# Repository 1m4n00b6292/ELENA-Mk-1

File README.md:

# ELENA Mk.1

**ELENA Mk.1** is a Raspberry Pi HAT built around an **STM32H562RGT6** (Cortex-M33, LQFP64). It sits between a
Raspberry Pi (developed against a Pi 5) and the robot's low-level hardware:

- The **Pi talks to the MCU over SPI**: fixed 64-byte frames with CRC, the MCU as SPI slave, plus a data-ready line.
- A **UART link to the Pi (or a USB-UART adapter)** gives a text console for bring-up, quick debugging and manual control.
- The MCU drives **four UNIDRIVE wheel drivers over CAN** (250 kbit/s) and samples a **TDK ICM-42688-P IMU** at 1 kHz.
- The board takes a **24 V-class supply** and generates 5 V (also fed to the Pi) and 3.3 V on board.

The firmware runs on **FreeRTOS** and is built in layers (L1 BSP → L2 RTOS + bus drivers → L3 device drivers →
L4 Pi link + parameters → L5 control). The current version is **0.4.0 (L4)**: the Pi link, telemetry and the
parameter store work; motion commands over SPI are refused until the L5 control layer lands.

---

## Contents

- [Hardware](#hardware)
- [Firmware architecture](#firmware-architecture)
- [SPI link protocol (Pi ⇄ MCU)](#spi-link-protocol-pi--mcu)
- [UART console](#uart-console)
- [CAN: UNIDRIVE wheel drivers](#can-unidrive-wheel-drivers)
- [Parameters](#parameters)
- [Status LEDs and fault codes](#status-leds-and-fault-codes)
- [Build and flash](#build-and-flash)
- [Host unit tests](#host-unit-tests)
- [Pi-side tool: `elena_link.py`](#pi-side-tool-elena_linkpy)
- [Bench tests](#bench-tests)
- [Repository layout](#repository-layout)
- [Known issues and notes](#known-issues-and-notes)

---

## Hardware

Schematic: [`ELENA_Mk_1.pdf`](ELENA_Mk_1.pdf) (KiCad 10, five sheets: top level, Protection, DC_Power,
MCU_STM32H562RGT6, CAN_TRANSCEIVER).

### Block overview

```
 VIN (J1) ──► Protection ──► +24V ──► LMR51450 buck ──► +5V ──┬──► Pi 5V (J2 pin 2)
              LM74502 + 2x CSD18510Q5B                         ├──► TJA1051T CAN transceiver
              TVS3301, SMBJ5371B                               └──► AP2112K-3.3 ──► +3V3 (MCU)

 Raspberry Pi header (J2) ◄── SPI0 + DRDY ──► STM32H562RGT6 ◄── SPI3 + I2C1 ──► J4 sensor header (ICM-42688-P)
                          ◄── UART ───────►               ──── FDCAN1 ─────► TJA1051T ──► J5 CANH/CANL
                                                          ──── SWD ────────► J3
```

### Power

| Stage | Part | Notes |
| --- | --- | --- |
| Input | J1 (2-pin) | VIN with LED indicator |
| Reverse / over-voltage protection | LM74502H controller driving back-to-back CSD18510Q5B MOSFETs | OV threshold set by R3/R4 (100 k / 3.5 k); TVS3301 (37 V abs max) and SMBJ5371B on the input |
| 24 V → 5 V | LMR51450 synchronous buck, 4.7 µH | Output +5V, test point TP2 |
| 5 V → 3.3 V | AP2112K-3.3 LDO | Output +3V3, test point TP3 |

The +5V rail is connected to the Pi header's 5V pin, so the HAT can power the Pi.

### MCU and clocks

- STM32H562RGT6, 8 MHz crystal (Y1) on PH0/PH1, PLL to **168 MHz** SYSCLK.
- 1 MB flash, 640 KB RAM (per the linker script).
- BOOT0 strapped through R8 (10 k), 100 nF on NRST.

### Pinout highlights

| Function | MCU pin | Connects to | Firmware |
| --- | --- | --- | --- |
| SPI1 NSS | PA4 | Pi GPIO8 / CE0 (header pin 24) | SPI1 slave, hardware NSS input |
| SPI1 SCK | PA5 | Pi GPIO11 / SCLK (pin 23) | |
| SPI1 MISO | PA6 | Pi GPIO9 / MISO (pin 21) | |
| SPI1 MOSI | PA7 | Pi GPIO10 / MOSI (pin 19) | |
| SPI1 DRDY | PC4 | Pi GPIO7 (pin 26) | GPIO output, "response ready" |
| USART1 TX | PB14 | Pi GPIO15 / RXD (pin 10) | 115200 8N1 console |
| USART1 RX | PB15 | Pi GPIO14 / TXD (pin 8) | |
| FDCAN1 RX / TX | PA11 / PA12 | TJA1051T (U6) → J5 | Classic CAN, 250 kbit/s |
| SPI3 SCK / MISO / MOSI | PC10 / PC11 / PC12 | J4 | SPI master, 6 MHz, mode 0 |
| SPI3 CS1 / CS2 / CS3 | PD2 / PB3 / PB4 | J4 | GPIO chip selects (CS1 = IMU) |
| I2C1 SCL / SDA | PB6 / PB7 | J4 | Configured, not used yet |
| SWDIO / SWCLK | PA13 / PA14 | J3 | Debug |
| LED_1 … LED_4 | PC3, PC2, PC1, PC0 | D6, D5, D4, D3 (510 Ω to GND) | See [LEDs](#status-leds-and-fault-codes) |

### Connectors

| Ref | Type | Pins |
| --- | --- | --- |
| J1 | 1x2 | Power input |
| J2 | Raspberry Pi 40-pin | 5V, GND, SPI0 (GPIO8–11), GPIO7 (DRDY), UART (GPIO14/15) |
| J3 | 1x3 SWD | 1 SWDIO, 2 SWCLK, 3 GND |
| J4 | 2x5 sensor header | 1 SDA, 2 SCL, 3 SPI3_CS3, 4 SPI3_CS2, 5 GND, 6 +5V, 7 SPI3_CS1, 8 SPI3_MOSI, 9 SPI3_MISO, 10 SPI3_SCK |
| J5 | 1x2 CAN | CANH, CANL. 120 Ω termination (R13) selectable with jumper JP1 |

> **J4 supply:** J4 only carries +5V, but the ICM-42688-P is rated 3.6 V max. Power the IMU module from 3.3 V
> (see [Known issues](#known-issues-and-notes)).

### IMU

TDK ICM-42688-P on SPI3 / CS1 (datasheet: [`ds-000347-icm-42688-p-v1.6.pdf`](ds-000347-icm-42688-p-v1.6.pdf)).
Default setup: accel ±4 g, gyro ±500 dps, both at 1 kHz ODR, low-noise mode. J4 has no interrupt line, so the
firmware polls it every 1 ms with a 14-byte burst read (about 20 µs at 6 MHz).

---

## Firmware architecture

STM32CubeMX project (`ELENA_Mk1_FW_V1.ioc`) with CMake, HAL, and a vendored **FreeRTOS V11.1.0** kernel
(port `ARM_CM33_NTZ`, non-secure, no TrustZone, `heap_4`). Application code lives in `App/` and is layered:

| Layer | Folder | What it does |
| --- | --- | --- |
| L1 BSP | `App/bsp/` | Reset cause, CPU fault capture (register dump on UART, kept in backup SRAM across a reset), LEDs, µs time base (TIM2), polled debug UART, IWDG |
| L2 bus drivers | `App/drivers/bus/` | USART1 with DMA both ways, SPI3 master, FDCAN1 with RX filters and a TX ring, CRC-16 on the CRC peripheral plus software CRC-16/CRC-8 |
| L3 device drivers | `App/drivers/dev/` | ICM-42688-P, UNIDRIVE CAN protocol (pure packing/parsing) and node tracking |
| L4 comms | `App/comms/` | SPI frame format (pure code), SPI1 slave link with DRDY, parameter table and flash storage |
| App | `App/app/` | Tasks, self-test, bring-up shell and console commands, LED blink codes, link application glue |
| OS | `App/os/` | `FreeRTOSConfig.h`, RTOS hooks |

Pure code (`spi_proto.c`, `unidrive_proto.c`, `params.c`, `crc_sw.c`) has no HAL or RTOS dependency and is unit
tested on a PC.

### Tasks (firmware 0.4.0)

| Task | Priority | Job |
| --- | --- | --- |
| `link` | 6 | SPI1 slave link to the Pi: validate each frame, answer, re-arm DMA, raise DRDY |
| `imu` | 4 | Poll the ICM-42688-P at 1 kHz, publish the latest sample, re-check WHO_AM_I every 100 ms |
| `canrx` | 3 | Hand each received CAN frame to the UNIDRIVE driver |
| `boot` | 2 | Start bus drivers, load parameters, run the self-test, start the other tasks, then run the console shell |
| `hb` | 1 | Every 20 ms: kick the IWDG, update LED blink codes; toggle the heartbeat LED at 1 Hz |

L5 adds the control task (state machine, kinematics, fault manager).

### Boot self-test

At every boot the firmware checks: software and peripheral CRC-16 and CRC-8 against their check values, UART TX
through DMA, CAN internal loopback into both FIFOs, CAN hardware filter rejection, and the IMU WHO_AM_I (0x47).
The result prints on the console and a failed internal check shows as LED blink code 4-1. Run it again any time
with `selftest`.

### Build-time switches

`App/Inc/config.h`:

| Switch | Meaning |
| --- | --- |
| `CFG_IWDG_ENABLE`, `CFG_IWDG_TIMEOUT_MS` | Independent watchdog on/off, timeout (100 ms) |
| `CFG_IWDG_FREEZE_IN_DEBUG` | Freeze the IWDG while the debugger halts the core |
| `CFG_HOST_WDT_ENABLE`, `CFG_HOST_TIMEOUT_MS` | Raise HOST_TIMEOUT if no valid SPI frame for 500 ms (off for bench work without a Pi) |
| `CFG_CMD_STALE_MS` | Ramp to zero when the newest drive command is older than this |
| `CFG_FAULT_RESET` | After a CPU fault: 1 = reset, 0 = halt and blink LED_3 so a debugger can attach |
| `CFG_TRAP_DIV_BY_ZERO` | Trap integer divide by zero as a UsageFault |
| `CFG_DRV_EXPECTED_MASK` | Which wheel driver nodes must be present (0x0F = all four) |
| `CFG_LED_UART_RX` | LED_2 flashes on console RX (until L5 uses it for ARMED) |
| `CFG_TEST_FAULT`, `CFG_TEST_IWDG` | Bench-only: deliberate BusFault / hang 5 s after boot |

Enable both watchdogs before running on the robot.

---

## SPI link protocol (Pi ⇄ MCU)

The Pi is SPI master (SPI0, CE0, mode 0, 8-bit, MSB first; the Pi tool defaults to 4 MHz). The MCU is the slave on
SPI1 with hardware NSS.

### Transaction flow

1. The MCU has a 64-byte response loaded and both DMAs armed, then raises **DRDY** (PC4 → Pi GPIO7).
2. The Pi asserts CE0 and clocks exactly 64 bytes each way. NSS falling drops DRDY.
3. NSS rising wakes the `link` task: it checks that exactly 64 bytes arrived, validates and handles the command,
   builds the next response, re-arms DMA and raises DRDY again.

The response clocked out during a transfer was prepared after the **previous** transfer, so the answer to a command
arrives in the next transaction. A transfer of any other length is aborted, counted, and answered with ACK result 6
(`SHORT`).

### Frame format (64 bytes, all fields little-endian)

| Bytes | Field | Notes |
| --- | --- | --- |
| 0 | SOF | `0xA5` |
| 1 | VER | `0x01` |
| 2 | TYPE | See below |
| 3 | SEQ | Sequence number |
| 4 | LEN | Payload length, must match the TYPE exactly |
| 5 | FLAGS | Response: bit 0 another param reply waiting, bit 1 faults latched |
| 6..61 | Payload | 56 bytes, zero-padded |
| 62..63 | CRC | CRC-16/CCITT-FALSE (poly 0x1021, init 0xFFFF) over bytes 0..61 |

### Commands (Pi → MCU)

| TYPE | Name | LEN | Payload |
| --- | --- | --- | --- |
| `0x00` | POLL | 0 | |
| `0x01` | DRIVE_TWIST | 8 | `vx`, `vy`, `wz` (i16), `accel_max` (u16, 0 = use parameter) |
| `0x02` | WHEEL_SPEED | 8 | 4 × i16, 0.1 rpm |
| `0x03` | WHEEL_DUTY | 8 | 4 × i16, 0.01 % |
| `0x10` | ARM | 3 | key `0x4D52`, arm (u8) |
| `0x11` | ESTOP | 0 | |
| `0x12` | CLEAR_FAULTS | 4 | mask (u32) |
| `0x20` | SET_PARAM | 6 | id (u16), value (f32) |
| `0x21` | GET_PARAM | 2 | id (u16) |
| `0x22` | SAVE_PARAMS | 2 | key `0x5356` |
| `0x7F` | REBOOT | 3 | key `0x5242`, target (u8) |

SET_PARAM, SAVE_PARAMS and REBOOT are refused while armed. At L4 the robot cannot be armed: ARM, DRIVE_TWIST,
WHEEL_SPEED and WHEEL_DUTY are answered `REFUSED`; ESTOP and CLEAR_FAULTS go straight to the drivers.

### Responses (MCU → Pi)

**TELEMETRY (`0x80`)**, payload offsets:

| Offset | Field | Type / unit |
| --- | --- | --- |
| 0 | ack_seq | u8, SEQ of the command being acknowledged |
| 1 | ack_result | u8: 0 OK, 1 BAD_CRC (also bad SOF/VER), 2 UNKNOWN_TYPE, 3 BAD_LEN, 4 REFUSED, 5 BAD_KEY, 6 SHORT |
| 2 | state | u8: 0 BOOT, 1 DISARMED, 2 ARMED, 3 ESTOP, 4 FAULT |
| 3 | drv_online | u8 bit mask of wheel drivers |
| 4 | faults | u32 bit mask |
| 8 | time_us | u32 |
| 12 | acc[3] | i16 raw counts |
| 18 | gyr[3] | i16 raw counts |
| 24 | imu_temp | i16 raw (°C = raw / 132.48 + 25) |
| 26 | wheel_spd[4] | i16, 0.1 rpm |
| 34 | wheel_pos[4] | i32, unwrapped encoder counts |
| 50 | motor_i[4] | u8, 0.1 A magnitude |
| 54 | vbus | u16, 10 mV |

**PARAM_REPLY (`0x81`)**: id (u16), status (0 OK, 1 UNKNOWN, 2 RANGE, 3 READONLY, 4 ARMED), value (f32).

**Fault bits** set at L4: 3 IMU_FAIL, 4–7 DRV1–4_OFFLINE, 8–11 DRV1–4_FAULT, 12 CAN_BUS_OFF, 13 CAN_ERR_PASSIVE,
18 WDT_RESET, 19 PARAM_INVALID.

### Pi setup

```
# /boot/firmware/config.txt
dtparam=spi=on
dtoverlay=spi0-1cs     # one chip select only, frees GPIO7 for DRDY
```

---

## UART console

USART1 at **115200 8N1**, no flow control, DMA in both directions. Reach it from the Pi's UART (GPIO14/15) or with a
3.3 V USB-UART adapter on PB14 (MCU TX) / PB15 (MCU RX). Set the terminal to treat `\r\n` as one newline.

After boot the console prints a banner (firmware version, SYSCLK, reset cause, watchdog state), the self-test
results and a `>` prompt. Type `help` for the full list.

| Group | Commands |
| --- | --- |
| System | `help`, `stat`, `top`, `selftest`, `faults`, `crc <text>`, `wdtstall`, `reboot` |
| IMU / SPI3 | `imu [reset]`, `imustream [hz]`, `spi <cs 1-3> <hex bytes>` |
| CAN | `cantx <id> [bytes]`, `canburst <n>`, `canmon`, `canping [count] [n]`, `canmode normal\|silent\|loop`, `canrecover` |
| Wheel drivers | `drv [clear]`, `drvspeed <n> <rpm> [s]`, `drvduty <n> <%> [s]`, `drvctl enable\|disable\|estop\|clear [n]`, `drvenc <n>`, `drvparam <n> read <idx> \| write <idx> <value> \| save` |
| Pi link (L4) | `link [clear\|raw]`, `linkmon`, `status` |
| Parameters (L4) | `param [list]`, `param get <id\|name>`, `param set <id\|name> <value>`, `param save`, `param defaults` |

---

## CAN: UNIDRIVE wheel drivers

FDCAN1 in classic CAN 2.0A mode at **250 kbit/s**. Four wheel driver nodes: 1 FL, 2 FR, 3 RL, 4 RR. CAN ID =
function code + node id; multi-byte fields are little-endian, and periodic frames end in a CRC-8/SAE-J1850 over
bytes 0..6.

| Function | Base ID | Direction |
| --- | --- | --- |
| CONTROL (enable, disable, e-stop, clear) | `0x000` | MCU → drivers |
| FAULT_EVENT | `0x080` | drivers → MCU |
| SPEED_CMD (coast, brake, speed, duty) | `0x200` | MCU → driver |
| FEEDBACK | `0x280` | driver → MCU |
| STATUS | `0x300` | driver → MCU |
| PARAM_RESP | `0x580` | driver → MCU |
| PARAM_REQ | `0x600` | MCU → driver |
| BOOT | `0x700` | driver → MCU |

Hardware filters accept only the driver-to-MCU IDs: FAULT_EVENT and FEEDBACK go to FIFO0, STATUS, PARAM_RESP and
BOOT to FIFO1. Both FIFOs drain into one 32-frame RTOS queue; transmit uses a 32-frame software ring so a 100 Hz
burst never blocks the caller. A node counts as online if any frame arrived in the last 300 ms.

---

## Parameters

16 float parameters, shared by SPI (`SET_PARAM` / `GET_PARAM` / `SAVE_PARAMS`) and the console (`param`). Each has a
range and a default. They are stored in the last 8 KB flash sector (bank 2) with a CRC; a missing or bad block loads
the defaults and raises `PARAM_INVALID` until the next successful save. IDs are stable: append only, never renumber.

| ID | Name | Default | Range | Unit |
| --- | --- | --- | --- | --- |
| 0 | table_version | – | read only | |
| 1 | track_width | 400 | 50–2000 | mm |
| 2 | wheel_diam | 150 | 20–1000 | mm |
| 3 | enc_cpr | 8192 | 1–1e6 | counts/rev |
| 4 | max_wheel_rpm | 300 | 1–3000 | rpm |
| 5 | accel_max | 1000 | 10–20000 | mm/s² |
| 6 | cmd_stale | 200 | 20–2000 | ms |
| 7 | host_timeout | 500 | 50–5000 | ms |
| 8 | drv_offline | 30 | 10–1000 | ms |
| 9 | vbus_low | 20 | 0–40 | V |
| 10 | vbus_high | 30 | 0–40 | V |
| 11 | tilt_max | 30 | 1–90 | deg |
| 12 | tilt_time | 200 | 0–5000 | ms |
| 13 | imu_accel_fs | 2 (±4 g) | 0–3 | 0 = 16 g … 3 = 2 g, next boot |
| 14 | imu_gyro_fs | 2 (±500 dps) | 0–4 | 0 = 2000 dps … 4 = 125 dps, next boot |
| 15 | spare15 | 0 | | reserved |

---

## Status LEDs and fault codes

| LED | Pin | Ref | Meaning |
| --- | --- | --- | --- |
| LED_1 | PC3 | D6 | Heartbeat, 1 Hz |
| LED_2 | PC2 | D5 | Flashes on console RX (becomes ARMED at L5) |
| LED_3 | PC1 | D4 | Fault blink codes (below); fast blink = CPU fault or RTOS assert |
| LED_4 | PC0 | D3 | Toggles every 10 valid SPI frames |

LED_3 blink codes: number of long flashes = subsystem, number of short flashes = problem. Codes clear by
themselves when the cause goes away; several faults are shown one after the other.

| Code | Meaning |
| --- | --- |
| 1-1 | Motor driver offline (an expected node not heard for 300 ms) |
| 1-2 | Motor driver reports FAULT or E-STOP |
| 2-1 | CAN bus-off |
| 2-2 | CAN error-passive (frames not ACKed: no other node, cable, termination) |
| 3-1 | IMU not answering |
| 4-1 | Boot self-test failed (stays until a `selftest` passes) |
| 5-1 | Console UART receiver not running for 200 ms |

---

## Build and flash

**Requirements:** STM32CubeMX (STM32CubeH5 package), Arm GNU toolchain (`arm-none-eabi-gcc`), CMake ≥ 3.22,
Ninja, and an ST-Link (or STM32CubeProgrammer). VS Code with the STM32 extension or STM32CubeIDE also work.

1. Open `firmware/ELENA_Mk1_FW_V1.ioc` in STM32CubeMX and **Generate Code** (toolchain: CMake). This creates the
   HAL drivers, startup file, `cmake/stm32cubemx/` and the CMake presets that the top-level `CMakeLists.txt` uses.
   The FreeRTOS kernel is vendored in `Middlewares/Third_Party/FreeRTOS` and is not managed by CubeMX.
2. Build:
   ```sh
   cd firmware
   cmake --preset Debug
   cmake --build --preset Debug
   ```
   Output: `build/Debug/ELENA_Mk1_FW_V1.elf`.
3. Flash over SWD (J3: SWDIO, SWCLK, GND), for example:
   ```sh
   STM32_Programmer_CLI -c port=SWD -w build/Debug/ELENA_Mk1_FW_V1.elf -v -rst
   ```
4. Open the console at 115200 8N1 and check the banner and self-test.

To decode a fault dump: `arm-none-eabi-addr2line -e build/Debug/ELENA_Mk1_FW_V1.elf <PC>`.

---

## Host unit tests

Hardware-independent code is tested on a PC with a normal C compiler (gcc, clang or MSVC; not the ARM toolchain):

```sh
cd firmware
cmake -S tests/host -B build-host
cmake --build build-host
ctest --test-dir build-host --output-on-failure
```

Four tests, all must pass:

| Test | Covers |
| --- | --- |
| `crc` | CRC-16/CCITT-FALSE (check 0x29B1) and CRC-8/SAE-J1850 (check 0x4B) |
| `unidrive` | UNIDRIVE CAN frame packing and parsing |
| `spi_proto` | SPI frame build/parse, rebuilds the spec's DRIVE_TWIST and TELEMETRY examples byte for byte |
| `params` | Parameter table, range checks, flash image build/parse |

---

## Pi-side tool: `elena_link.py`

`firmware/tools/pi_link/elena_link.py` drives the SPI link from the Pi for testing.

```sh
sudo apt install python3-spidev python3-libgpiod
python3 elena_link.py selftest              # no hardware: frame/CRC check against the spec examples
python3 elena_link.py status                # one decoded TELEMETRY
python3 elena_link.py poll -n 5000 -r 500   # POLL at 500 Hz, error statistics
python3 elena_link.py watch                 # live telemetry, 5 Hz
python3 elena_link.py list | get 1 | set 1 450 | save
python3 elena_link.py estop | clear | arm | drive 200 0
python3 elena_link.py badcrc | badlen | short | reboot
```

Options: `--hz` SPI clock (default 4 MHz), `--no-drdy` (fixed 1 ms wait instead of the DRDY pin),
`--drdy-gpio N` (default 7), `--chip /dev/gpiochipX` (auto-detected on the Pi 5). Supports libgpiod v1 and v2.

---

## Bench tests

[`firmware/docs/BENCH_TESTS.md`](firmware/docs/BENCH_TESTS.md) has a step-by-step test plan per firmware layer, with
expected console output, checkboxes and a results log. Run every test of a layer before moving to the next.

| Layer | Tests |
| --- | --- |
| L1 BSP | Boot banner and clock, LEDs, fault capture, IWDG |
| L2 RTOS + bus | Self-test, tasks/stack/CPU load, UART DMA, SPI3 chip selects, CAN TX/RX/filters/bus-off, watchdog under FreeRTOS |
| L3 devices | IMU readout and recovery, UNIDRIVE presence, SPEED_CMD/FEEDBACK, faults, parameters, LED blink codes |
| L4 Pi link | Link task and parameter block, flash save, first contact from the Pi, POLL stress, bad-frame rejection, parameters over SPI, robot commands, telemetry |

Common setup: bench supply (no Pi needed until L4), ST-Link on SWD, USB-UART on USART1 at 115200 8N1.

### F103 CAN tester / UNIDRIVE emulator

[`firmware/tools/can_tester_f103/`](firmware/tools/can_tester_f103/README.md) turns an STM32F103C8 + TJA1051T board
into a second CAN node for the L2 tests (ACK, logging, burst checks, echo mode for `canping`) and an emulator of
the four UNIDRIVE wheel drivers for L3, so the driver code can be tested before the real driver boards exist. Its
README covers wiring, CubeMX setup and commands.

---

## Repository layout

```
.
├── README.md
├── ELENA_Mk_1.pdf                    Schematic
├── ds-000347-icm-42688-p-v1.6.pdf    ICM-42688-P datasheet
└── firmware/
    ├── ELENA_Mk1_FW_V1.ioc           STM32CubeMX project
    ├── CMakeLists.txt
    ├── STM32H562xx_FLASH.ld          Linker script
    ├── Core/                         CubeMX-generated main.c and interrupt handlers
    ├── App/
    │   ├── Inc/config.h              Build-time switches
    │   ├── bsp/                      L1: reset, faults, LEDs, time, debug UART, watchdog
    │   ├── drivers/bus/              L2: UART DMA, SPI3, FDCAN, CRC, HAL callbacks
    │   ├── drivers/dev/              L3: ICM-42688-P, UNIDRIVE
    │   ├── comms/                    L4: SPI protocol and link, parameters
    │   ├── app/                      Tasks, shell, self-test, status LED, link glue
    │   └── os/                       FreeRTOSConfig.h, hooks
    ├── Middlewares/Third_Party/FreeRTOS/   FreeRTOS V11.1.0 kernel (vendored)
    ├── tests/host/                   PC unit tests (CTest)
    ├── tools/
    │   ├── pi_link/elena_link.py     Pi-side SPI link test tool
    │   └── can_tester_f103/          F103 CAN tester and UNIDRIVE emulator
    └── docs/BENCH_TESTS.md           Bench test plan and results
```

---

## Known issues and notes

- **J4 has no 3.3 V pin.** The ICM-42688-P is rated 3.6 V max; powering the IMU module from J4's +5V made it fail
  and also disturbed UART receive on the MCU. Feed the module from 3.3 V. Next revision: add +3V3 to J4.
- **J3 (SWD) has SWDIO, SWCLK and GND only**: no NRST and no 3.3 V reference pin.
- **No IMU interrupt line** on J4, so the IMU is polled at 1 kHz.
- **Watchdogs:** `CFG_IWDG_ENABLE` and `CFG_HOST_WDT_ENABLE` must both be 1 on the robot.
- **L5 (control) is not implemented yet**: the robot cannot be armed and motion commands over SPI are refused.

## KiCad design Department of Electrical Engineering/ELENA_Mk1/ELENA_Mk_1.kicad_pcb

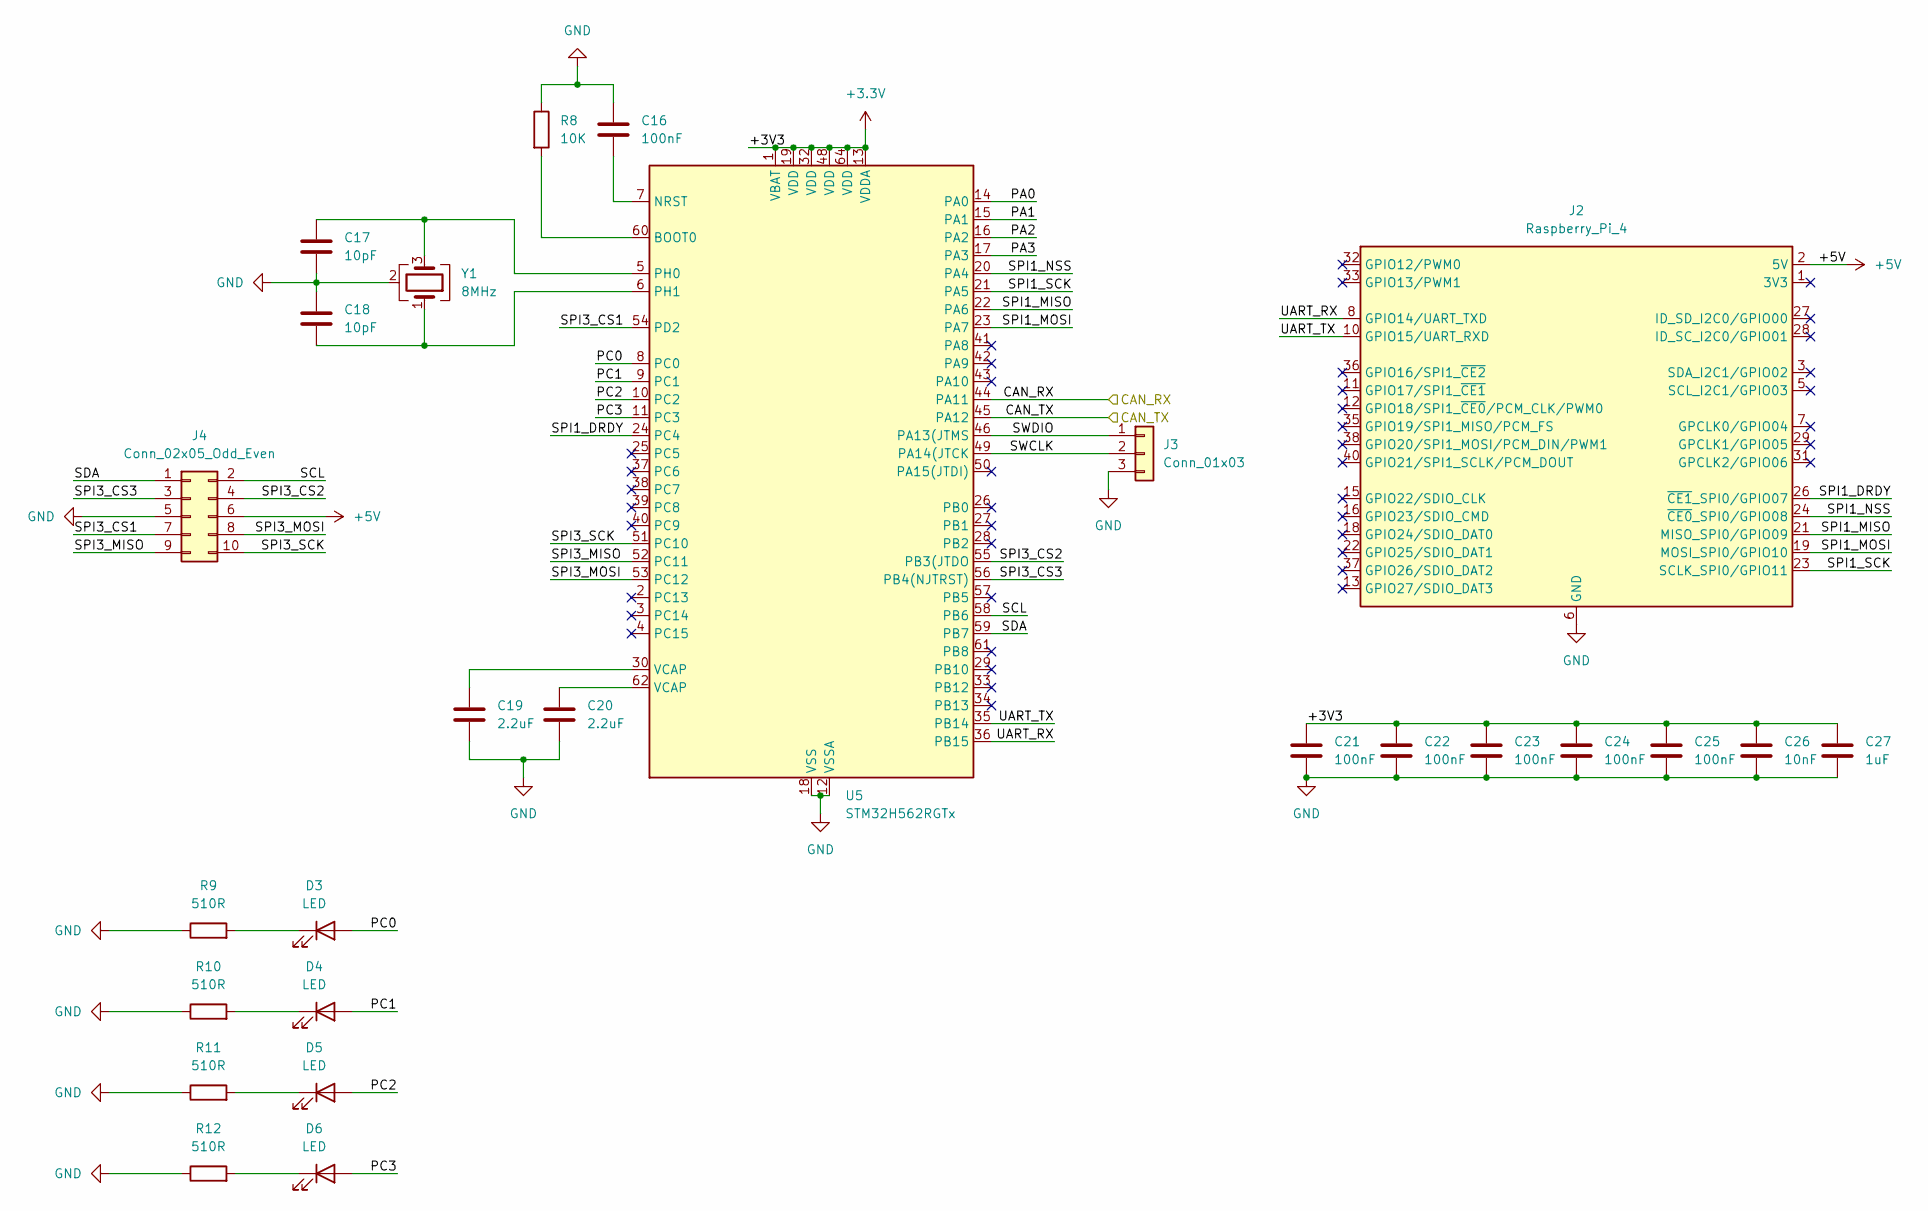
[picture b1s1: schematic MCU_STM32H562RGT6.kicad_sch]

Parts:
C16, C21, C22, C23, C24, C25: 100nF; C_0603_1608Metric_Pad1.08x0.95mm_HandSolder
C17, C18: 10pF; C_0603_1608Metric_Pad1.08x0.95mm_HandSolder
C19, C20: 2.2uF; C_0603_1608Metric_Pad1.08x0.95mm_HandSolder
C26: 10nF; C_0603_1608Metric_Pad1.08x0.95mm_HandSolder
C27: 1uF; C_0603_1608Metric_Pad1.08x0.95mm_HandSolder
D3, D4, D5, D6: LED; LED_1206_3216Metric_Pad1.42x1.75mm_HandSolder
J2: Raspberry_Pi_4; PinSocket_2x20_P2.54mm_Vertical
J3: Conn_01x03; PinHeader_1x03_P2.54mm_Vertical
J4: Conn_02x05_Odd_Even; PinHeader_2x05_P2.54mm_Vertical
R8: 10K; R_0603_1608Metric_Pad0.98x0.95mm_HandSolder
R9, R10, R11, R12: 510R; R_0603_1608Metric_Pad0.98x0.95mm_HandSolder
U5: STM32H562RGTx; LQFP-64_10x10mm_P0.5mm
Y1: 8MHz; Crystal_SMD_3225-4Pin_3.2x2.5mm

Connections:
+3.3V: C21.1, C22.1, C23.1, C24.1, C25.1, C26.1, C27.1, U5.1 (VBAT), U5.13 (VDDA), U5.19 (VDD), U5.32 (VDD), U5.48 (VDD), U5.64 (VDD); also elsewhere on the board
+5V: J2.2 (5V), J2.4 (5V), J4.6; also elsewhere on the board
/CAN_TRANSCEIVER/CAN_RX: U5.44 (PA11); also elsewhere on the board
/CAN_TRANSCEIVER/CAN_TX: U5.45 (PA12); also elsewhere on the board
/MCU_STM32H562RGT6/PA0: U5.14 (PA0)
/MCU_STM32H562RGT6/PA1: U5.15 (PA1)
/MCU_STM32H562RGT6/PA2: U5.16 (PA2)
/MCU_STM32H562RGT6/PA3: U5.17 (PA3)
/MCU_STM32H562RGT6/PC0: D3.2 (A), U5.8 (PC0)
/MCU_STM32H562RGT6/PC1: D4.2 (A), U5.9 (PC1)
/MCU_STM32H562RGT6/PC2: D5.2 (A), U5.10 (PC2)
/MCU_STM32H562RGT6/PC3: D6.2 (A), U5.11 (PC3)
/MCU_STM32H562RGT6/SCL: J4.2, U5.58 (PB6)
/MCU_STM32H562RGT6/SDA: J4.1, U5.59 (PB7)
/MCU_STM32H562RGT6/SPI1_DRDY: J2.26 (~CE1_SPI0/GPIO07), U5.24 (PC4)
/MCU_STM32H562RGT6/SPI1_MISO: J2.21 (MISO_SPI0/GPIO09), U5.22 (PA6)
/MCU_STM32H562RGT6/SPI1_MOSI: J2.19 (MOSI_SPI0/GPIO10), U5.23 (PA7)
/MCU_STM32H562RGT6/SPI1_NSS: J2.24 (~CE0_SPI0/GPIO08), U5.20 (PA4)
/MCU_STM32H562RGT6/SPI1_SCK: J2.23 (SCLK_SPI0/GPIO11), U5.21 (PA5)
/MCU_STM32H562RGT6/SPI3_CS1: J4.7, U5.54 (PD2)
/MCU_STM32H562RGT6/SPI3_CS2: J4.4, U5.55 (PB3(JTDO)
/MCU_STM32H562RGT6/SPI3_CS3: J4.3, U5.56 (PB4(NJTRST))
/MCU_STM32H562RGT6/SPI3_MISO: J4.9, U5.52 (PC11)
/MCU_STM32H562RGT6/SPI3_MOSI: J4.8, U5.53 (PC12)
/MCU_STM32H562RGT6/SPI3_SCK: J4.10, U5.51 (PC10)
/MCU_STM32H562RGT6/SWCLK: J3.2, U5.49 (PA14(JTCK)
/MCU_STM32H562RGT6/SWDIO: J3.1, U5.46 (PA13(JTMS)
/MCU_STM32H562RGT6/UART_RX: J2.8 (GPIO14/UART_TXD), U5.36 (PB15)
/MCU_STM32H562RGT6/UART_TX: J2.10 (GPIO15/UART_RXD), U5.35 (PB14)
GND: C16.1, C17.2, C18.1, C19.2, C20.2, C21.2, C22.2, C23.2, C24.2, C25.2, C26.2, C27.2, J2.6 (GND), J2.9 (GND), J2.14 (GND), J2.20 (GND), J2.25 (GND), J2.30 (GND), J2.34 (GND), J2.39 (GND), J3.3, J4.5, R8.1, R9.1, R10.1, R11.1, R12.1, U5.12 (VSSA), U5.18 (VSS), U5.31 (VSS), U5.47 (VSS), U5.63 (VSS), Y1.2 (G), Y1.4 (G); also elsewhere on the board
unnamed: C19.1, U5.30 (VCAP)
unnamed: C20.1, U5.62 (VCAP)
unnamed: D3.1 (K), R9.2
unnamed: D4.1 (K), R10.2
unnamed: D5.1 (K), R11.2
unnamed: D6.1 (K), R12.2
unnamed: R8.2, U5.60 (BOOT0)
unnamed: C16.2, U5.7 (NRST)
unnamed: C17.1, U5.5 (PH0), Y1.3
unnamed: C18.2, U5.6 (PH1), Y1.1

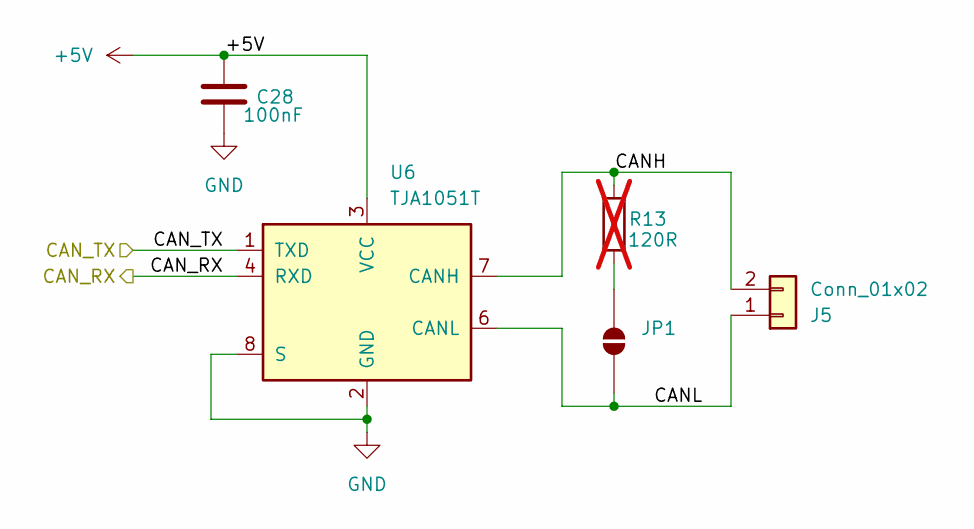
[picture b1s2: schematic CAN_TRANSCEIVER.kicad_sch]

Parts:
C28: 100nF; C_0603_1608Metric_Pad1.08x0.95mm_HandSolder
J5: Conn_01x02; TerminalBlock_Phoenix_MKDS-1,5-2-5.08_1x02_P5.08mm_Horizont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
JP1: SolderJumper_2_Open; SolderJumper-2_P1.3mm_Open_TrianglePad1.0x1.5mm
R13: 120R; R_0603_1608Metric_Pad0.98x0.95mm_HandSolder; not fitted
U6: TJA1051T; SOIC-8_3.9x4.9mm_P1.27mm

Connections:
+5V: C28.1, U6.3 (VCC); also elsewhere on the board
/CAN_TRANSCEIVER/CANH: J5.2, R13.1, U6.7 (CANH)
/CAN_TRANSCEIVER/CANL: J5.1, JP1.1 (A), U6.6 (CANL)
/CAN_TRANSCEIVER/CAN_RX: U6.4 (RXD); also elsewhere on the board
/CAN_TRANSCEIVER/CAN_TX: U6.1 (TXD); also elsewhere on the board
GND: C28.2, U6.2 (GND), U6.8 (S); also elsewhere on the board
unnamed: JP1.2 (B), R13.2

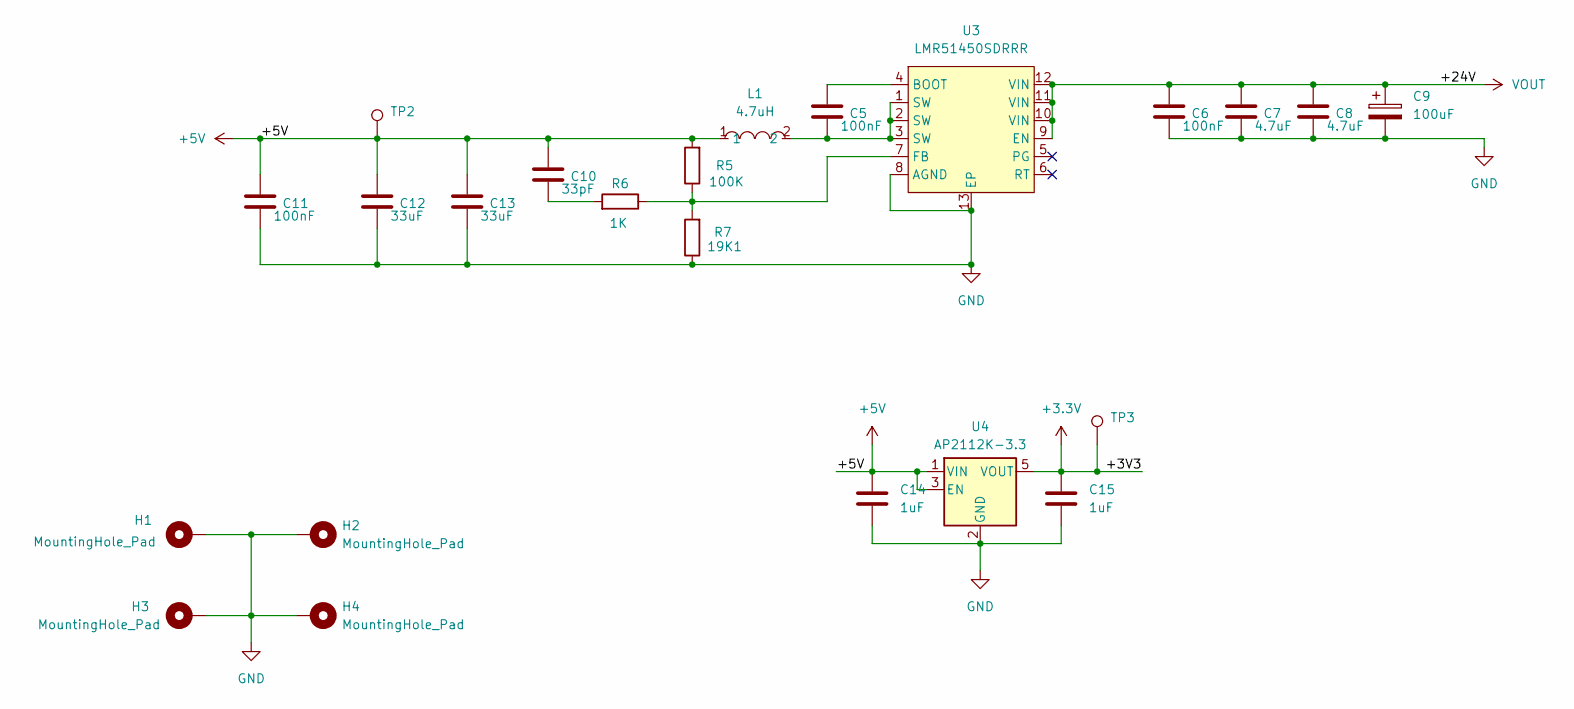
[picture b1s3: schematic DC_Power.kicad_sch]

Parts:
C5, C6, C11: 100nF; C_0603_1608Metric_Pad1.08x0.95mm_HandSolder
C7, C8: 4.7uF; C_0603_1608Metric_Pad1.08x0.95mm_HandSolder
C9: 100uF; CP_Elec_8x6.5
C10: 33pF; C_0603_1608Metric_Pad1.08x0.95mm_HandSolder
C12, C13: 33uF; C_0805_2012Metric_Pad1.18x1.45mm_HandSolder
C14, C15: 1uF; C_0603_1608Metric_Pad1.08x0.95mm_HandSolder
H1, H2, H3, H4: MountingHole_Pad; MountingHole_3.2mm_M3_DIN965_Pad_TopBottom
L1: 4.7uH; IND-SMD_L5.4-W5.2_FXL0530; MPN FXL0530-4R7-M; LCSC Part C177246
R5: 100K; R_0603_1608Metric_Pad0.98x0.95mm_HandSolder
R6: 1K; R_0603_1608Metric_Pad0.98x0.95mm_HandSolder
R7: 19K1; R_0603_1608Metric_Pad0.98x0.95mm_HandSolder
TP2, TP3: TestPoint; TestPoint_Pad_D2.0mm
U3: LMR51450SDRRR; WSON-12_L3.0-W3.0-P0.50-TL-EP-2; MPN LMR51450SDRRR; LCSC Part C6890985
U4: AP2112K-3.3; SOT-23-5

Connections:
+3.3V: C15.1, TP3.1 (1_1), U4.5 (VOUT); also elsewhere on the board
+5V: C10.1, C11.1, C12.1, C13.1, C14.1, L1.1, R5.2, TP2.1 (1_1), U4.1 (VIN), U4.3 (EN); also elsewhere on the board
GND: C6.2, C7.2, C8.2, C9.2, C11.2, C12.2, C13.2, C14.2, C15.2, H1.1 (1_1), H2.1 (1_1), H3.1 (1_1), H4.1 (1_1), R7.1, U3.8 (AGND), U3.13 (EP), U4.2 (GND); also elsewhere on the board
unnamed: C5.2, L1.2, U3.1 (SW), U3.2 (SW), U3.3 (SW)
unnamed: C10.2, R6.2
unnamed: C5.1, U3.4 (BOOT)
unnamed: R5.1, R6.1, R7.2, U3.7 (FB)
VOUT: C6.1, C7.1, C8.1, C9.1, U3.9 (EN), U3.10 (VIN), U3.11 (VIN), U3.12 (VIN); also elsewhere on the board

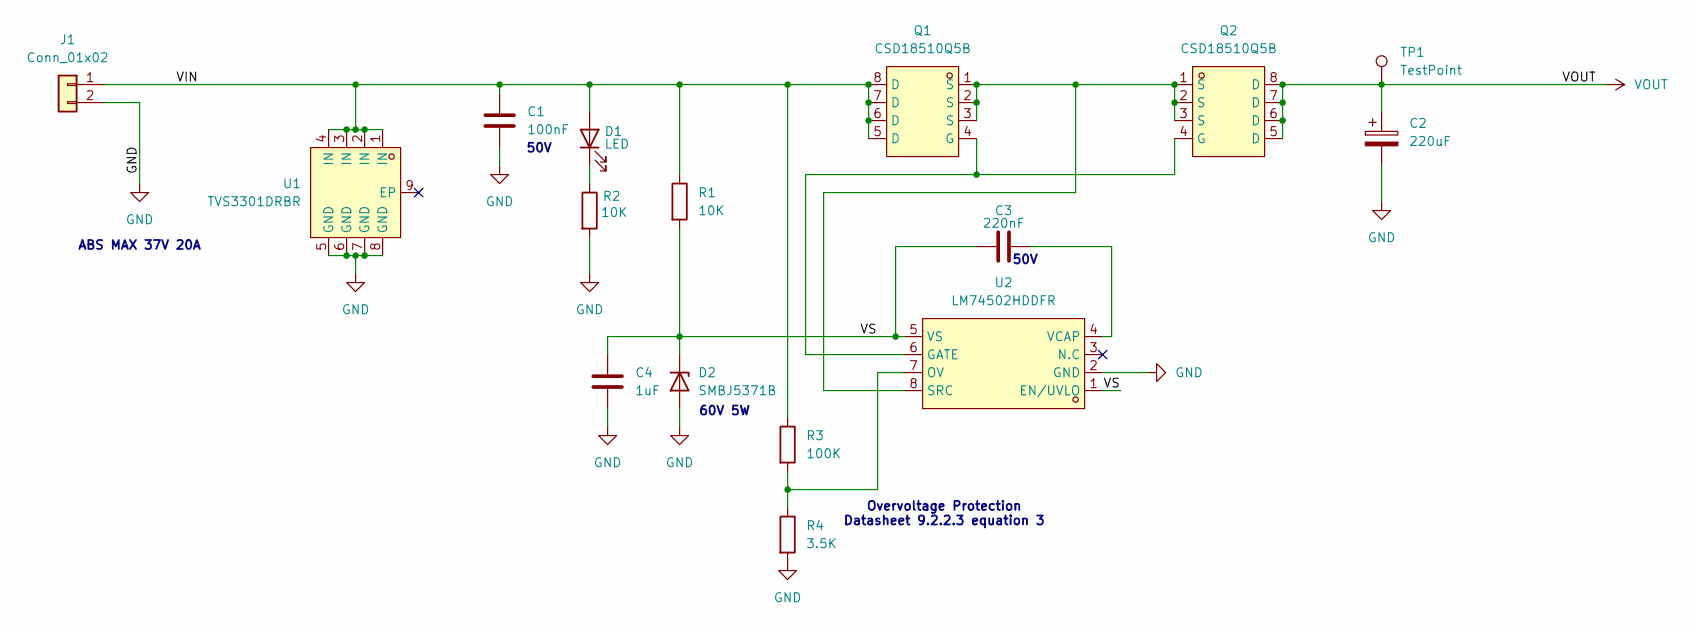
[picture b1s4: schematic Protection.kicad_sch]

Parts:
C1: 100nF; C_1206_3216Metric
C2: 220uF; CP_Radial_D8.0mm_P3.80mm
C3: 220nF; C_0603_1608Metric_Pad1.08x0.95mm_HandSolder
C4: 1uF; C_1206_3216Metric
D1: LED; LED_1206_3216Metric
D2: SMBJ5371B; D_SMB_Handsoldering
J1: Conn_01x02; PhoenixContact_GMSTBA_2,5_2-G-7,62_1x02_P7.62mm_Horizontal
Q1, Q2: CSD18510Q5B; VSON-CLIP-8_L6.0-W5.0-P1.27-BL; MPN CSD18510Q5B; LCSC Part C2876544
R1, R2: 10K; R_1206_3216Metric
R3: 100K; C_0603_1608Metric_Pad1.08x0.95mm_HandSolder
R4: 3.5K; C_0603_1608Metric_Pad1.08x0.95mm_HandSolder
TP1: TestPoint; TestPoint_Pad_D1.5mm
U1: TVS3301DRBR; VSON-8_L3.0-W3.0-P0.65-BL-EP; MPN TVS3301DRBR; LCSC Part C2864392
U2: LM74502HDDFR; SOT-23-8_L2.9-W1.6-P0.65-LS2.8-BL; MPN LM74502HDDFR; LCSC Part C5219202

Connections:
/Protection/VIN: C1.1, D1.2 (A), J1.1, Q1.5 (D), Q1.6 (D), Q1.7 (D), Q1.8 (D), R1.1, R3.1, U1.1 (IN), U1.2 (IN), U1.3 (IN), U1.4 (IN)
/Protection/VS: C3.1, C4.1, D2.1 (K), R1.2, U2.1 (EN/UVLO), U2.5 (VS)
GND: C1.2, C2.2, C4.2, D2.2 (A), J1.2, R2.2, R4.2, U1.5 (GND), U1.6 (GND), U1.7 (GND), U1.8 (GND), U2.2 (GND); also elsewhere on the board
unnamed: D1.1 (K), R2.1
unnamed: Q1.4 (G), Q2.4 (G), U2.6 (GATE)
unnamed: R3.2, R4.1, U2.7 (OV)
unnamed: Q1.1 (S), Q1.2 (S), Q1.3 (S), Q2.1 (S), Q2.2 (S), Q2.3 (S), U2.8 (SRC)
unnamed: C3.2, U2.4 (VCAP)
VOUT: C2.1, Q2.5 (D), Q2.6 (D), Q2.7 (D), Q2.8 (D), TP1.1 (1_1); also elsewhere on the board

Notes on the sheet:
ABS MAX 37V 20A
60V 5W
Overvoltage Protection Datasheet 9.2.2.3 equation 3
50V

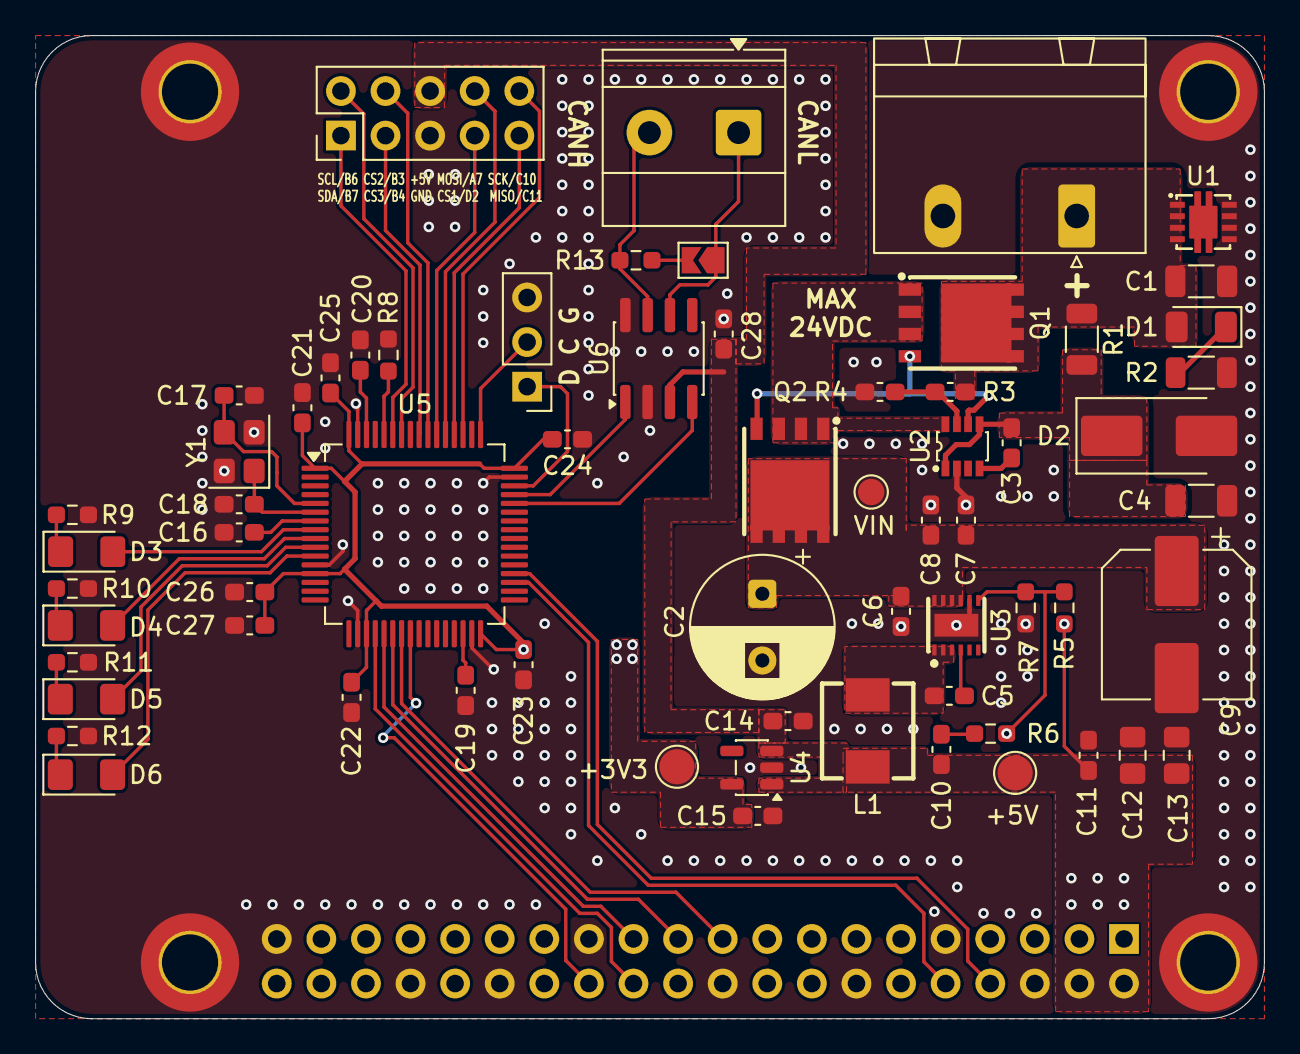
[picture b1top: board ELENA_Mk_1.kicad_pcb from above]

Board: 2 copper layers, 70.0 x 56.0 mm, 70 parts (1 on the bottom side), 51 nets.
